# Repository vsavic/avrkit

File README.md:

# Cycle Alpha - AVR Programmer Board - Quick Start Guide
**AVR-based microcontroller board, designed to help in small to medium production run**.

## Board Overview

This board is designed to be a portable, stand-alone programmer tool. We can store pre-compiled HEX files on SD card and burn them on new ATMega328 MCU.

Board supports DIP and SMD version of ATMega328 MCU via ZIF28 and TQFP32 sockets. Also there’s a direct ICSP line connected to these sockets via master \ slave jumper switch configuration.

Here’s a quick summary of some of the most important parts of the board:

1. SD Card
2. 5-Way Joystick
3. Button B
4. USB
5. Button A
6. 1.8” TFT Display
7. Power Jack
8. ICSP Header
9. Slave \ Master Selector
10. TQFP-32 SMT Socket
11. ZIF28 DIP Socket

Please refer to the image below to match the numbers with the coresponding components.

## Communcation
Board can be re-programmed via ICSP header, or directly via USB port.

It contains 1.8” TFT display which can be used with an on-board 5-way joystick in order to select the proper firmware which can be flashed on new MCU.

There’s also 2 additional buttons which are used to burn bootloader and to make a backup of the current code from the target MCU.

## Power
Board can be powered via USB cable or with external power supply battery connected to DC jack from 7 to 25 V DC. 

## Roadmap
* Add support to burn bootloader from EEPROM.
* Add support to store current target MCU firmware into EEPROM for further clonning.

At the moment, we can make a backup of the current firmware from target MCU by using "B" button on the board. Firmware will be stored on micro SD card as `Backup.hex` file.

## Notes
Common problem with some micro SD cards is that some of them cannot be initialized. In case that you get an serror screen with your SD card, follow the instruction. For more details, see `serial` console output.

SD card must be in FAT16 or FAT32 format in order to work with [SdFat](https://github.com/greiman/SdFat) library.

I tried a few different manufacturers, but the most reliable results I got with are with a Kingston 8GB class 10 micro SD card.

In case that you need to re-format your card, use this [SD Formatter](https://www.sdcard.org/downloads/formatter_4/index.html).

If you decide to modify the current firmware, keep in mind that SRAM is already very low.

Check this article for more details on [arduino memory problems](https://learn.adafruit.com/memories-of-an-arduino?view=all).

Also, here's one more really good article about [PROGMEM](http://www.gammon.com.au/progmem).

## Special Thanks

Special thanks to [Nick Gammon](https://www.gammon.com.au/contactus.htm), without him, his original project and amazing articles, this board wouldn't exist.

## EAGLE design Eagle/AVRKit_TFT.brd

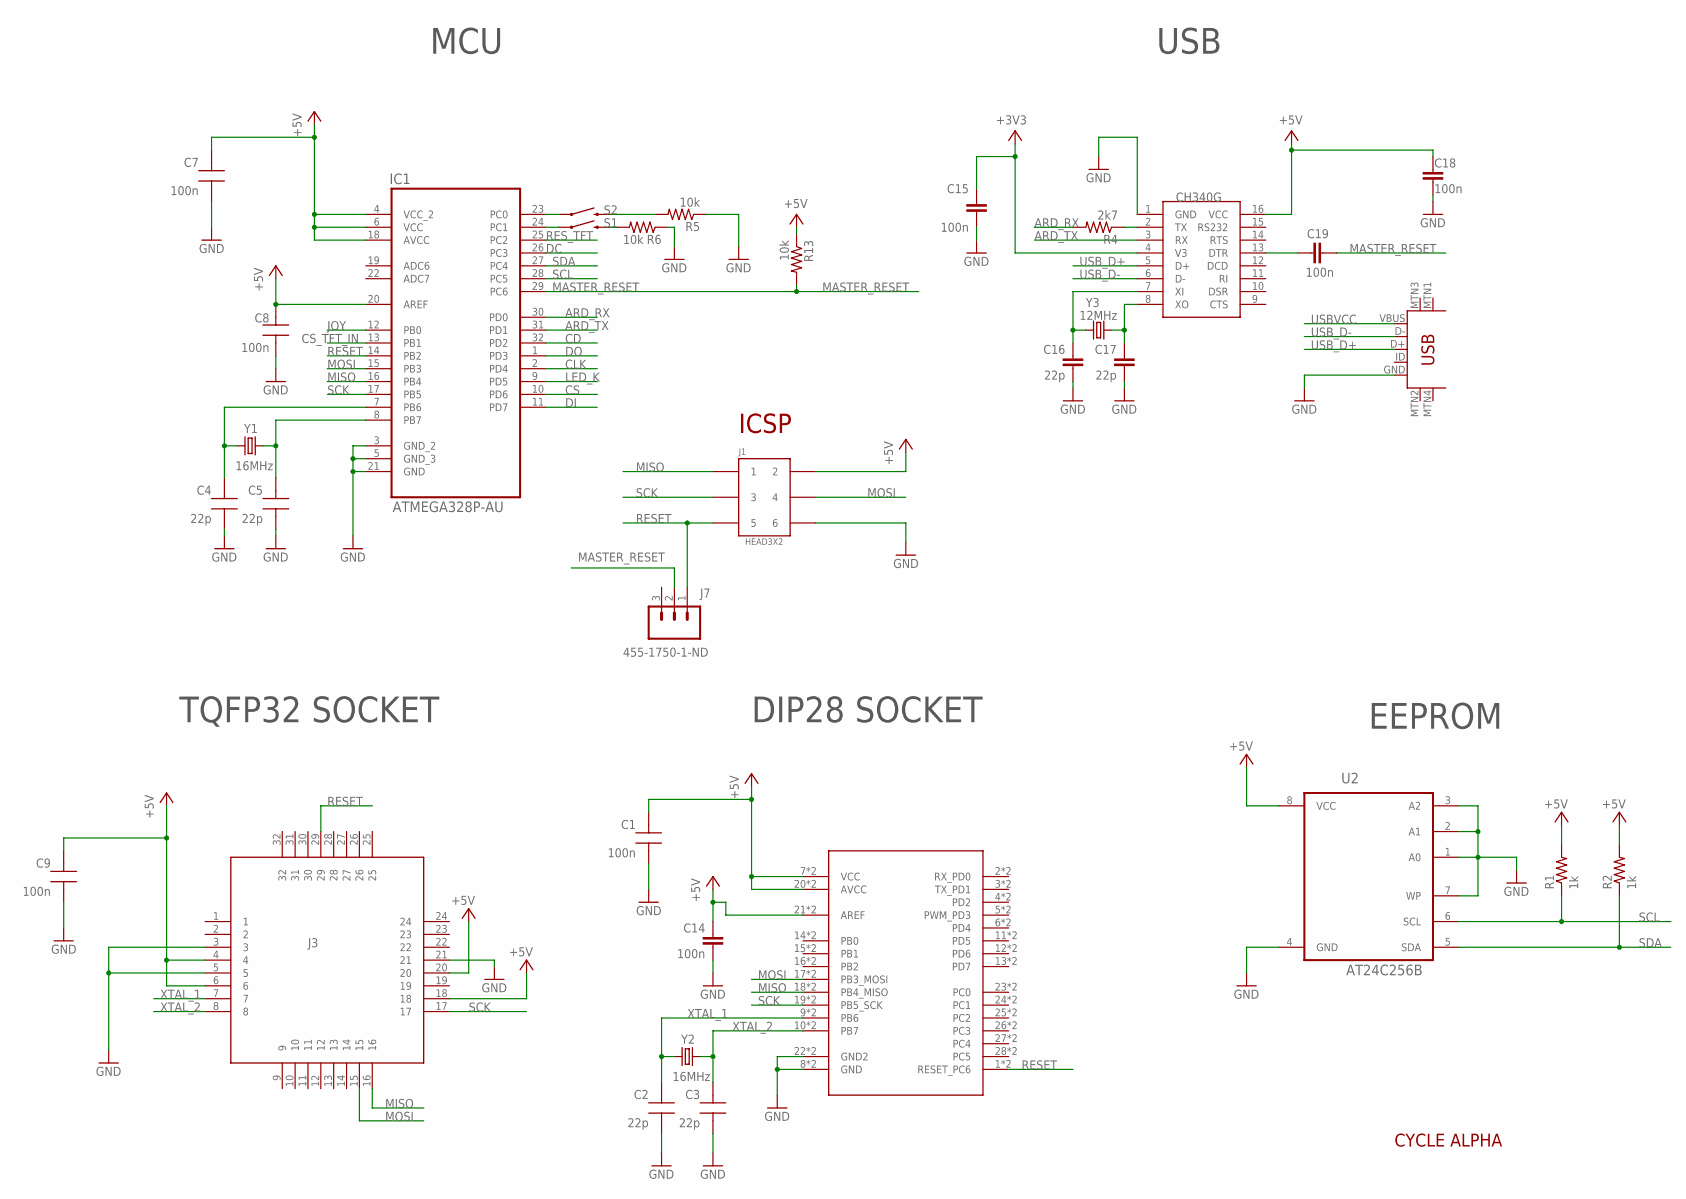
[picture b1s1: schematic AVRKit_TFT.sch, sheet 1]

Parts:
C1, C7, C8, C9: 100n; CAP0805-NP
C2, C3, C4, C5: 22p; CAP0805-NP
C14, C15, C18, C19: 100n; 0805
C16, C17: 22p; 0805
IC1: ATMEGA328P-AU; QFP80P900X900X120-32N
J1: HEAD3X2
J3: TQFP32_ADAPTER
J4: _ZIF28ADAPTER_2ROWS; DIL28_2ROWS
J5: USB-MINIB-5PIN; USB-MINIB
J7: 455-1750-1-ND; 1X03
R1, R2: 1k; R0805@1
R4: 2k7; R0805@1
R5, R6, R13: 10k; R0805@1
S1, S2: SWITCH-MOMENTARY-2SMD-4; TACTILE_SWITCH_TALL
U1: 0; SOIC16
U2: AT24C256B; SOIC8
Y1, Y2: 16MHz; CRYSTAL-SMD-5X3
Y3: 12MHz; CRYSTAL-SMD-5X3

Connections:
+3V3: C15.2, U1.4 (V3); also elsewhere on the board
+5V: C1.1, C7.1, C8.1, C9.1, C14.1, C18.2, IC1.4 (VCC_2), IC1.6 (VCC), IC1.18 (AVCC), IC1.20 (AREF), J1.2, J3.4, J3.6, J3.18, J3.20, J4.7 (VCC), J4.20 (AVCC), J4.21 (AREF), J4.107 (VCC), J4.120 (AVCC), J4.121 (AREF), R1.2, R2.2, R13.1, U1.16 (VCC), U2.8 (VCC); also elsewhere on the board
ARD_RX: IC1.30 (PD0), R4.2
ARD_TX: IC1.31 (PD1), U1.3 (RX)
CD: IC1.32 (PD2); also elsewhere on the board
CLK: IC1.2 (PD4); also elsewhere on the board
CS: IC1.10 (PD6); also elsewhere on the board
CS_TFT_IN: IC1.13 (PB1); also elsewhere on the board
DC: IC1.26 (PC3); also elsewhere on the board
DI: IC1.11 (PD7); also elsewhere on the board
DO: IC1.1 (PD3); also elsewhere on the board
GND: C1.2, C2.2, C3.2, C4.2, C5.2, C7.2, C8.2, C9.2, C14.2, C15.1, C16.2, C17.2, C18.1, IC1.3 (GND_2), IC1.5 (GND_3), IC1.21 (GND), J1.6, J3.3, J3.5, J3.21, J4.8 (GND), J4.22 (GND2), J4.108 (GND), J4.122 (GND2), J5.GND, R5.1, R6.1, U1.1 (GND), U2.1 (A0), U2.2 (A1), U2.3 (A2), U2.4 (GND), U2.7 (WP); also elsewhere on the board
JOY: IC1.12 (PB0); also elsewhere on the board
LED_K: IC1.9 (PD5); also elsewhere on the board
MASTER_RESET: C19.1, IC1.29 (PC6), J7.2, R13.2
MISO: IC1.16 (PB4), J1.1, J3.16, J4.18 (PB4_MISO), J4.118 (PB4_MISO)
MOSI: IC1.15 (PB3), J1.4, J3.15, J4.17 (PB3_MOSI), J4.117 (PB3_MOSI); also elsewhere on the board
unnamed: IC1.23 (PC0), S2.A2 (1)
unnamed: IC1.24 (PC1), S1.A2 (1)
unnamed: R5.2, S2.B2 (2)
unnamed: R6.2, S1.B2 (2)
unnamed: C19.2, U1.13 (DTR)
unnamed: R4.1, U1.2 (TX)
OSC3: C4.1, IC1.7 (PB6), Y1.3 (2)
OSC4: C5.1, IC1.8 (PB7), Y1.1
RESET: IC1.14 (PB2), J1.5, J3.29, J4.1 (RESET_PC6), J4.101 (RESET_PC6), J7.1
RES_TFT: IC1.25 (PC2); also elsewhere on the board
SCK: IC1.17 (PB5), J1.3, J3.17, J4.19 (PB5_SCK), J4.119 (PB5_SCK); also elsewhere on the board
SCL: IC1.28 (PC5), R1.1, U2.6 (SCL)
SDA: IC1.27 (PC4), R2.1, U2.5 (SDA)
USBVCC: J5.VBUS; also elsewhere on the board
USB_D+: J5.D+, U1.5 (D+)
USB_D-: J5.D-, U1.6 (D-)
XI1: C16.1, U1.7 (XI), Y3.1
XO1: C17.1, U1.8 (XO), Y3.3 (2)
XTAL_1: C2.1, J3.7, J4.9 (PB6), J4.109 (PB6), Y2.3 (2)
XTAL_2: C3.1, J3.8, J4.10 (PB7), J4.110 (PB7), Y2.1

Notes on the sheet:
USB
DIP28 SOCKET
MCU
EEPROM
TQFP32 SOCKET
ICSP
CYCLE ALPHA

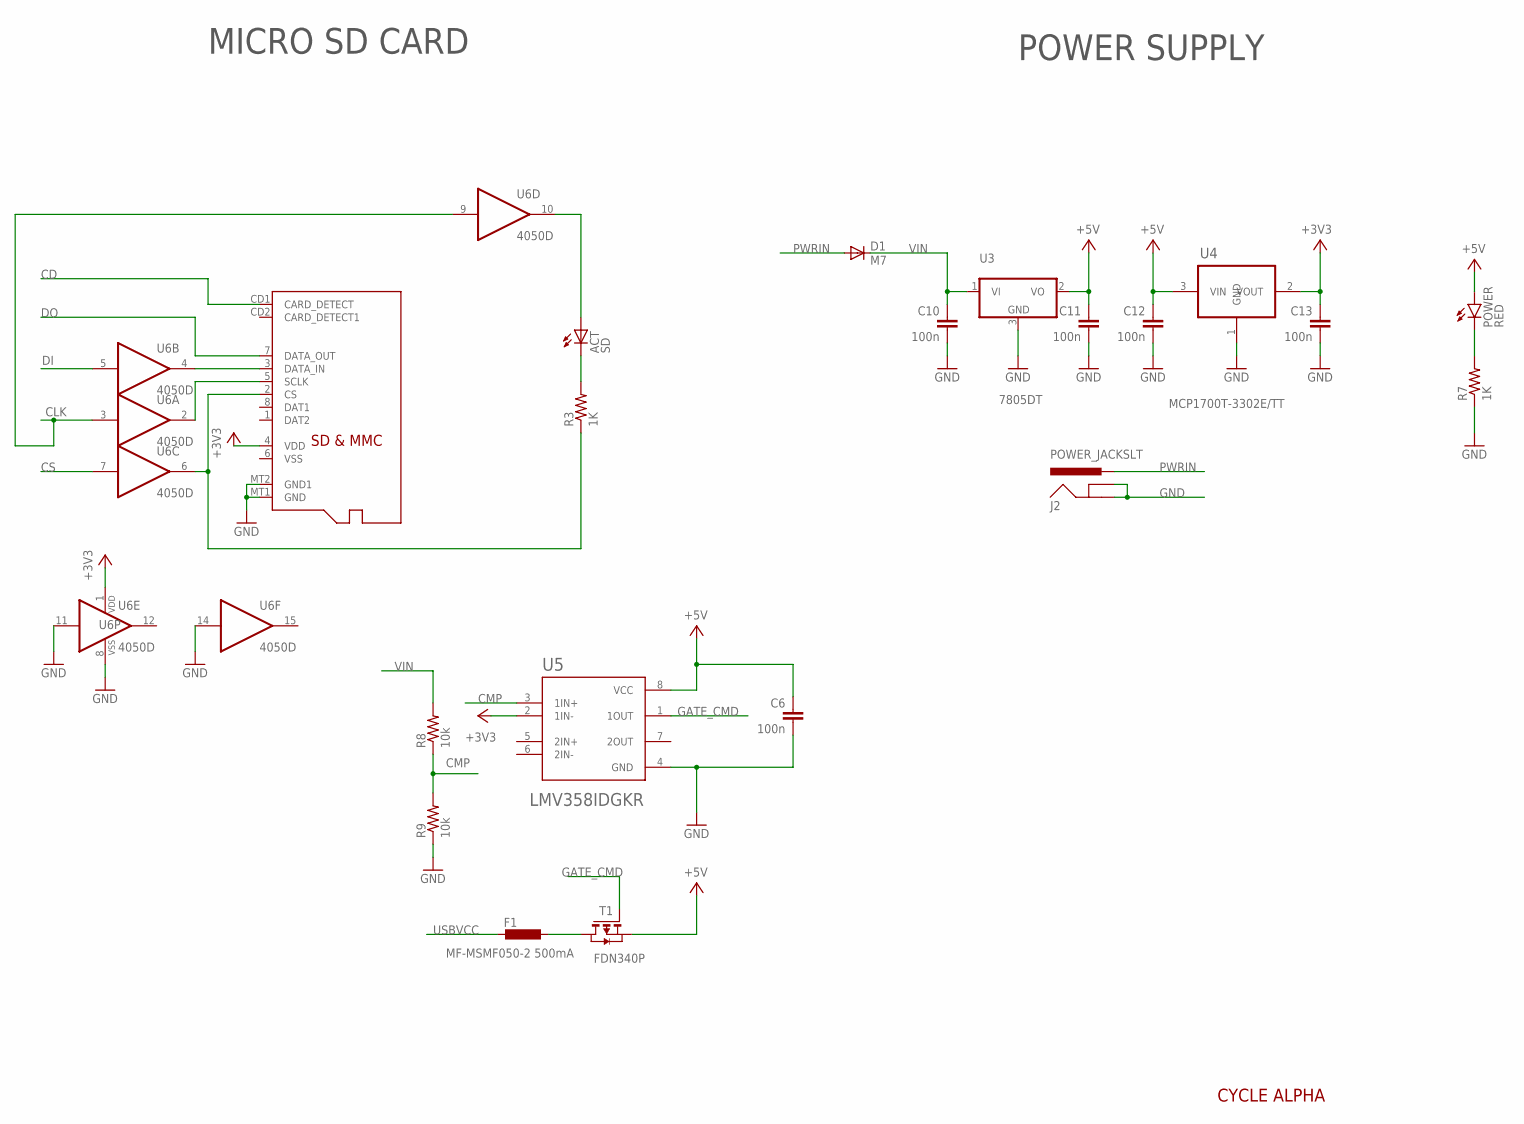
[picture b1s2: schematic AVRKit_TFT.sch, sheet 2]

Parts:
ACT: SD; CHIP-LED0805
C6, C10, C11, C12, C13: 100n; 0805
D1: M7; SMB
F1: MF-MSMF050-2 500mA; L1812
J2: POWER_JACKSLT; POWER_JACK_SLOT
J6: MICROSD_FOOTPRINT_2
POWER: RED; LED-1206
R3, R7: 1K; R0805
R8, R9: 10k; R0805
T1: FDN340P; SOT-23
U3: 7805DT; TO252
U4: MCP1700T-3302E/TT; SOT95P237X112-3N
U5: LMV358IDGKR; SOP65P490X110-8N
U6: 4050D; SO16

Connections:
+3V3: C13.1, J6.4 (VDD), U4.2 (VOUT), U5.2 (1IN-), U6.1 (VDD); also elsewhere on the board
+5V: C6.1, C11.1, C12.1, POWER.A, T1.2 (S), U3.2 (VO), U4.3 (VIN), U5.8 (VCC); also elsewhere on the board
CD: J6.CD1 (CARD_DETECT); also elsewhere on the board
CLK: U6.3 (I), U6.9 (I); also elsewhere on the board
CMP: R8.1, R9.2, U5.3 (1IN+)
CS: U6.7 (I); also elsewhere on the board
DI: U6.5 (I); also elsewhere on the board
DO: J6.7 (DATA_OUT); also elsewhere on the board
GATE_CMD: T1.3 (G), U5.1 (1OUT)
GND: C6.2, C10.2, C11.2, C12.2, C13.2, J2.GND@1 (GNDBREAK), J2.GND@2 (GND), J6.MT1 (GND), J6.MT2 (GND1), R7.1, R9.1, U3.3 (GND), U4.1 (GND), U5.4 (GND), U6.8 (VSS), U6.11 (I), U6.14 (I); also elsewhere on the board
unnamed: ACT.A, U6.10 (O)
unnamed: J6.5 (SCLK), U6.2 (O)
unnamed: J6.2 (CS), R3.1, U6.6 (O)
unnamed: ACT.C, R3.2
unnamed: J6.3 (DATA_IN), U6.4 (O)
unnamed: POWER.C, R7.2
unnamed: F1.1, T1.1 (D)
PWRIN: D1.A, J2.PWR
USBVCC: F1.2; also elsewhere on the board
VIN: C10.1, D1.C, R8.2, U3.1 (VI)

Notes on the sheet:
MICRO SD CARD
POWER SUPPLY
CYCLE ALPHA

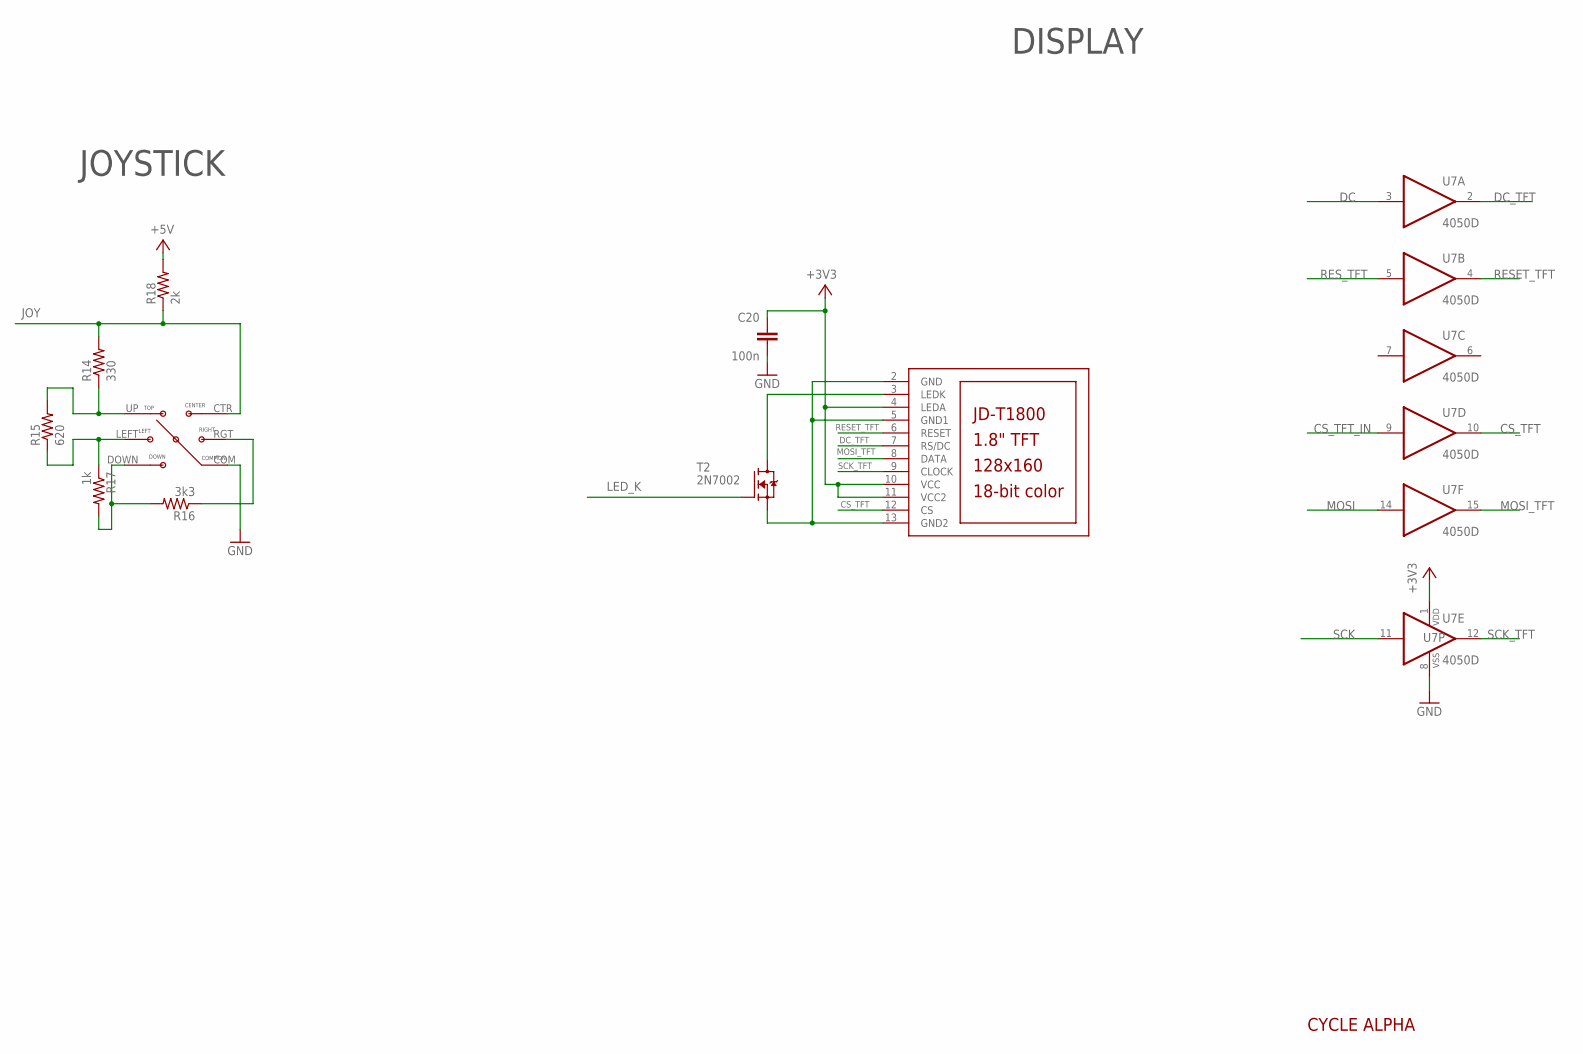
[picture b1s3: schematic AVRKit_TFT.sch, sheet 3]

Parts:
C20: 100n; 0805
LCD1: JD-T1800
R14: 330; R0805
R15: 620; R0805
R16: 3k3; R0805
R17: 1k; R0805
R18: 2k; R0805
T2: 2N7002; SOT23
U7: 4050D; SO16
U$3: JOG-SWITCH-5-WAY-SMD; JOG-SWITCH-10MM-SMD

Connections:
+3V3: C20.2, LCD1.4 (LEDA), LCD1.10 (VCC), LCD1.11 (VCC2), U7.1 (VDD); also elsewhere on the board
+5V: R18.2; also elsewhere on the board
CS_TFT: LCD1.12 (CS), U7.10 (O)
CS_TFT_IN: U7.9 (I); also elsewhere on the board
DC: U7.3 (I); also elsewhere on the board
DC_TFT: LCD1.7 (RS/DC), U7.2 (O)
GND: C20.1, LCD1.2 (GND), LCD1.5 (GND1), LCD1.13 (GND2), T2.2 (S), U7.8 (VSS), U$3.COM; also elsewhere on the board
JOY: R14.2, R18.1, U$3.CTR; also elsewhere on the board
LED_K: T2.1 (G); also elsewhere on the board
MOSI: U7.14 (I); also elsewhere on the board
MOSI_TFT: LCD1.8 (DATA), U7.15 (O)
unnamed: LCD1.3 (LEDK), T2.3 (D)
unnamed: R14.1, R15.2, U$3.UP
unnamed: R15.1, R17.1, U$3.LEFT
unnamed: R16.2, R17.2, U$3.DOWN
unnamed: R16.1, U$3.RGT
RESET_TFT: LCD1.6 (RESET), U7.4 (O)
RES_TFT: U7.5 (I); also elsewhere on the board
SCK: U7.11 (I); also elsewhere on the board
SCK_TFT: LCD1.9 (CLOCK), U7.12 (O)

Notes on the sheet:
JOYSTICK
DISPLAY
CYCLE ALPHA

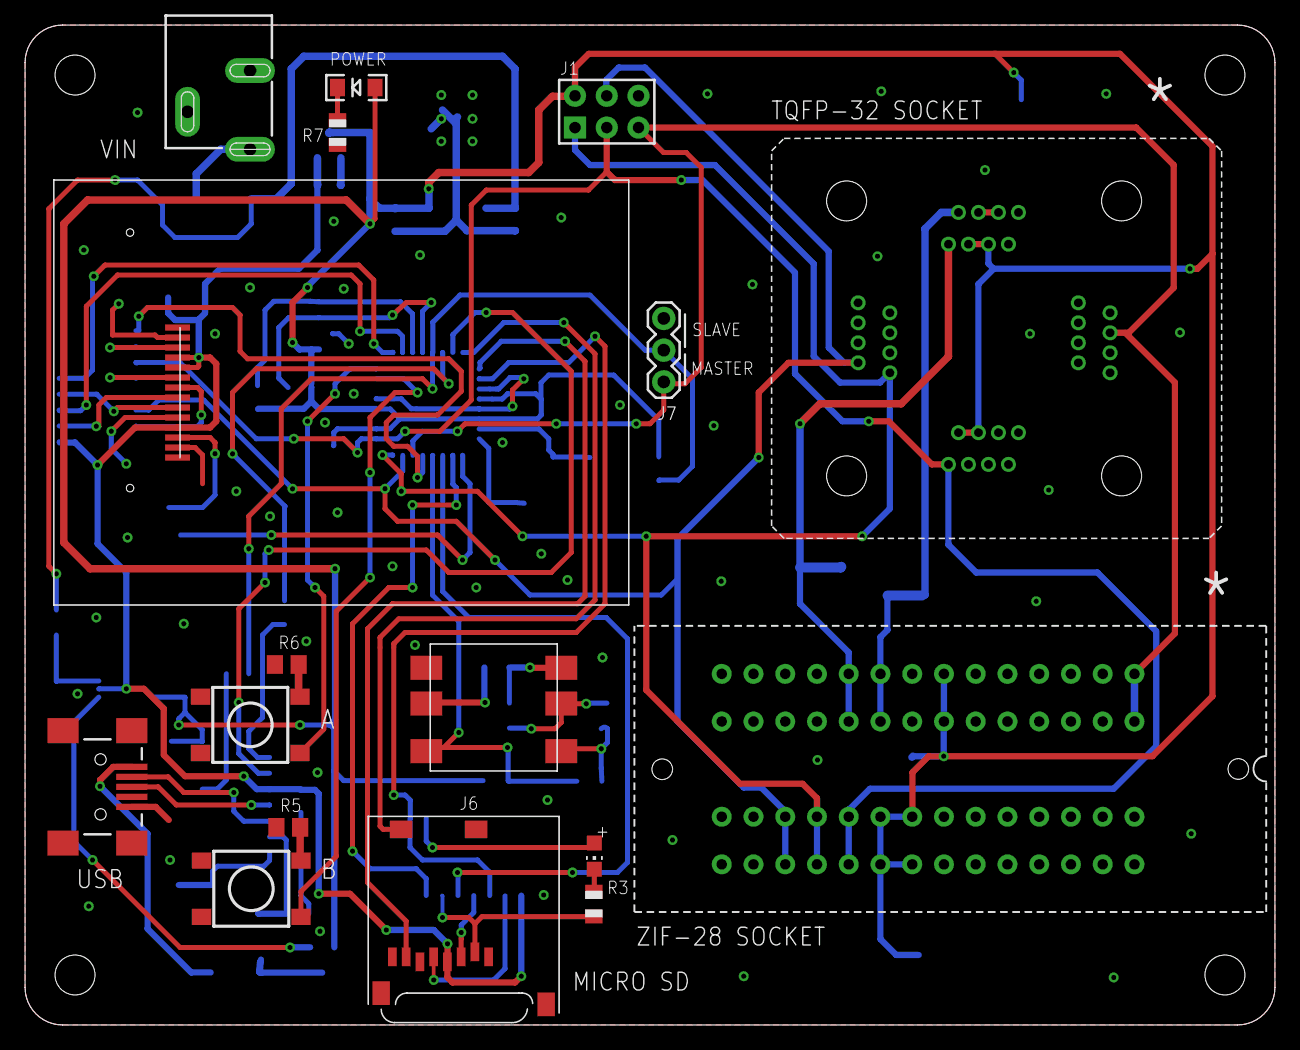
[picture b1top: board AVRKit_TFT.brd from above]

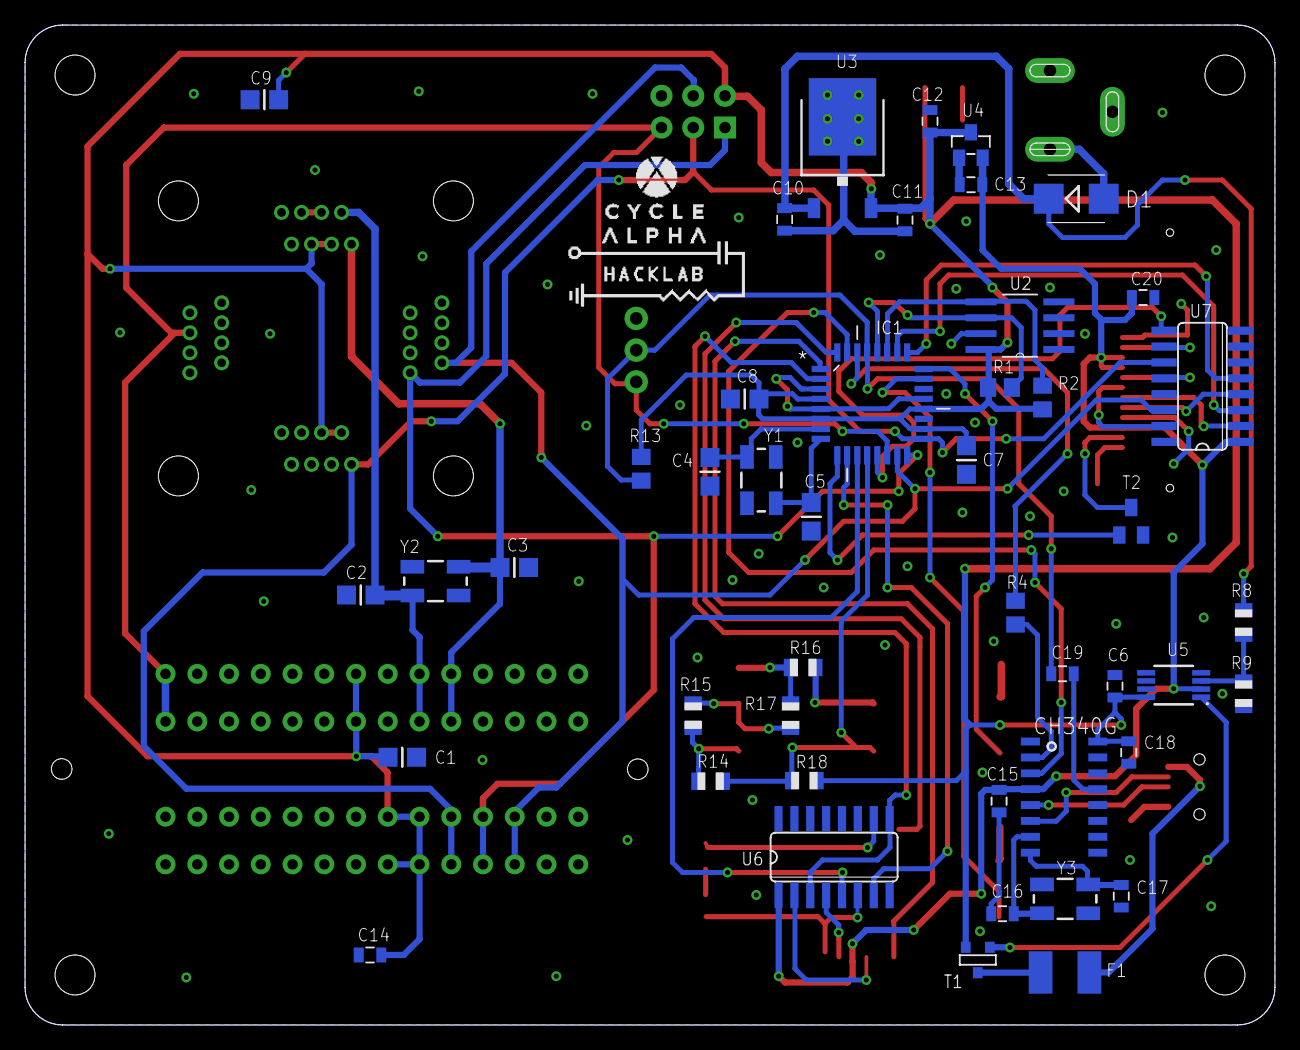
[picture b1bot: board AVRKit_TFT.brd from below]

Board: 2 copper layers, 100.0 x 80.0 mm, 64 parts (47 on the bottom side), 58 nets.

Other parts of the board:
U$4: LOGO_CYCLE_ALPHA_HACKLAB_14X12_MM

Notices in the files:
parts and their libraries:
SparkFun-Capacitors: Licensing: Creative Commons ShareAlike 4.0 International - https://creativecommons.org/licenses/by-sa/4.0
